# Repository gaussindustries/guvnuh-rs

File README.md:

# Guv'nuh — Micro-Grid Governor Control Platform

A Rust, bare-metal-to-browser control system for a laboratory micro-grid generator set. A hard-real-time STM32H753 governs the machine; an ESP32 bridges it to a Dioxus server and a desktop operator console. Built as the engineering centerpiece for [Gauss Industries](https://gaussindustri.es).

---

## What it does

Guv'nuh closes the loop on a self-excited induction generator (SEIG) driven by a variable-speed prime mover: it holds speed and frequency against changing electrical load, sheds load safely on fault, and streams a full electrical picture — per-phase voltage and current, real power, power factor, DC-bus state — to an operator in real time.

The architecture follows one principle: **the STM32 runs the machine; everything else observes and commands.** Safety-critical decisions (overspeed, load rejection, over-voltage/current) are computed and acted on locally, on-device, with no dependence on the network being up. The ESP32 relays; the server stores; the terminal analyzes. Comms can drop without the machine ever losing control.

---

## System architecture

```
  ┌─────────────┐   UART/COBS    ┌──────────┐    TCP/COBS    ┌──────────────┐   HTTP    ┌───────────────┐
  │  STM32H753  │◄──────────────►│  ESP32   │◄──────────────►│ Dioxus Server│◄─────────►│ Desktop Term. │
  │  (RTIC 2)   │  telemetry ▲   │ (Embassy)│  telemetry ▲   │   + SurrealDB│           │  (Dioxus)     │
  │  the machine│  commands  ▼   │  bridge  │  commands  ▼   │   store/API  │           │  operator UI  │
  └─────────────┘                └──────────┘                └──────────────┘           └───────────────┘
        │
        ├─ dual ADS131M04 (3-phase V/I + DC bus) — coherent sampling
        ├─ TIM1 PWM → prime-mover drive
        ├─ TIM2 QEI → speed encoder
        └─ ordered load bank (2-step resistive, series-ground)
```

**One wire format, end to end.** Every hop serializes the same `shared` crate types with `postcard` + COBS framing — no translation layers, no schema drift between tiers (the whole set rebuilds together when the wire types change).

---

## The STM32H753 firmware — the real-time core

Written against **RTIC 2**, priority-scheduled so the machine stays in tolerance regardless of what else is happening:

| Priority | Task | Rate | Job |
|---|---|---|---|
| 3 | ADC DRDY ISR | ~4 kSPS | Read both ADCs coherently, accumulate sum-of-squares |
| 3 | UART4 RX ISR | event | Drain FIFO, COBS-decode commands into a queue |
| 2 | Safety supervisor | 500 Hz | Overspeed trip + fast electrical protection + load-rejection detection |
| 1 | Control loop | 100 Hz | Governing, full ADC finalize, telemetry assembly |

**Three-phase electrical measurement.** Two ADS131M04 24-bit delta-sigma ADCs share one SPI bus with tied SYNC lines, so all eight channels sample the *same instant* — essential for real-power math (V×I per phase must be coherent). The STM32 computes only the control-critical scalars locally (RMS V/I, real power, PF, frequency, DC bus); harmonics and deep analysis are left to the terminal. Sample rate is a single tunable constant, sized against measured worst-case execution time.

**Load rejection — the fast local path.** A sudden real-power drop means the generator has been unloaded and will overspeed (the defining hazard for a turbine prime mover). The 500 Hz supervisor watches total real power and reacts in-loop — shedding load and faulting — with no network round-trip. This is why the electrical measurements live on the STM32 and not just in telemetry.

**Ordered load bank.** A two-step resistive bank whose second stage draws its ground return *through* the first, so the switching order is a hard electrical constraint. The firmware models this as a state machine that makes an invalid state unrepresentable: it refuses to engage step 2 without step 1, sheds gracefully (2 then 1) under normal operation, and sheds immediately (open 1, dropping both) on E-stop or fault.

---

## The ESP32 bridge

An **Embassy** async firmware that does one job well: shuttle framed bytes between the STM32's UART and a TCP socket to the server, intercepting the link-layer handshake locally so a reboot on either side re-syncs without disturbing the machine. Deliberately dumb — it holds no control logic, matching the "STM32 runs the machine" principle.

---

## Server & operator console

**Dioxus fullstack server** (axum + SurrealDB): ingests telemetry over TCP, stores trials, and exposes a hardware-control API. Telemetry x-axes are derived from a **server-side frame index**, not the device clock — eliminating boot-offset artifacts by construction.

**Desktop operator terminal** (Dioxus): live governing controls (manual / open-loop / closed-loop / scripted profiles), real-time charts (RPM, three-phase voltage and current on shared axes, power and phase-alignment error), a load-bank panel that mirrors the firmware's ordered state machine in the UI, and a trials browser that replays any recorded run with every electrical channel toggleable.

**Scripted profiles** let an operator define an RPM trajectory with load steps scheduled at specific breakpoints — "at t=5s apply half load, at t=10s go full, at t=15s shed" — executed on-device with the ordered switching still enforced.

---

## Tech stack

- **Firmware:** Rust, `no_std`, RTIC 2 (STM32H753), Embassy (ESP32)
- **Wire format:** `postcard` + COBS over UART and TCP; shared type crate
- **Server:** Rust, Dioxus fullstack, axum, SurrealDB (raw HTTP transport)
- **Terminal:** Rust, Dioxus desktop
- **Sensing:** dual TI ADS131M04, external 8.192 MHz coherent clock
- **Networking:** WireGuard-gated admin plane, nginx reverse proxy

---

## Status

Operational: full command + telemetry pipeline live across all four tiers; load bank commanding end-to-end with ordered-switching and E-stop shedding verified in hardware; governing loop running closed on the bench. Three-phase ADC front-end is wired into the firmware (flag-gated) and pending analog front-end bring-up.

**Roadmap:** phase-lock to a grid reference (the alignment view is built and waiting), EtherCAT fieldbus, a SIL-2 certification path, and a micro steam turbine prime mover.

---

## License

© Gauss Industries. All rights reserved.

*Integrity · Innovation · Invention*

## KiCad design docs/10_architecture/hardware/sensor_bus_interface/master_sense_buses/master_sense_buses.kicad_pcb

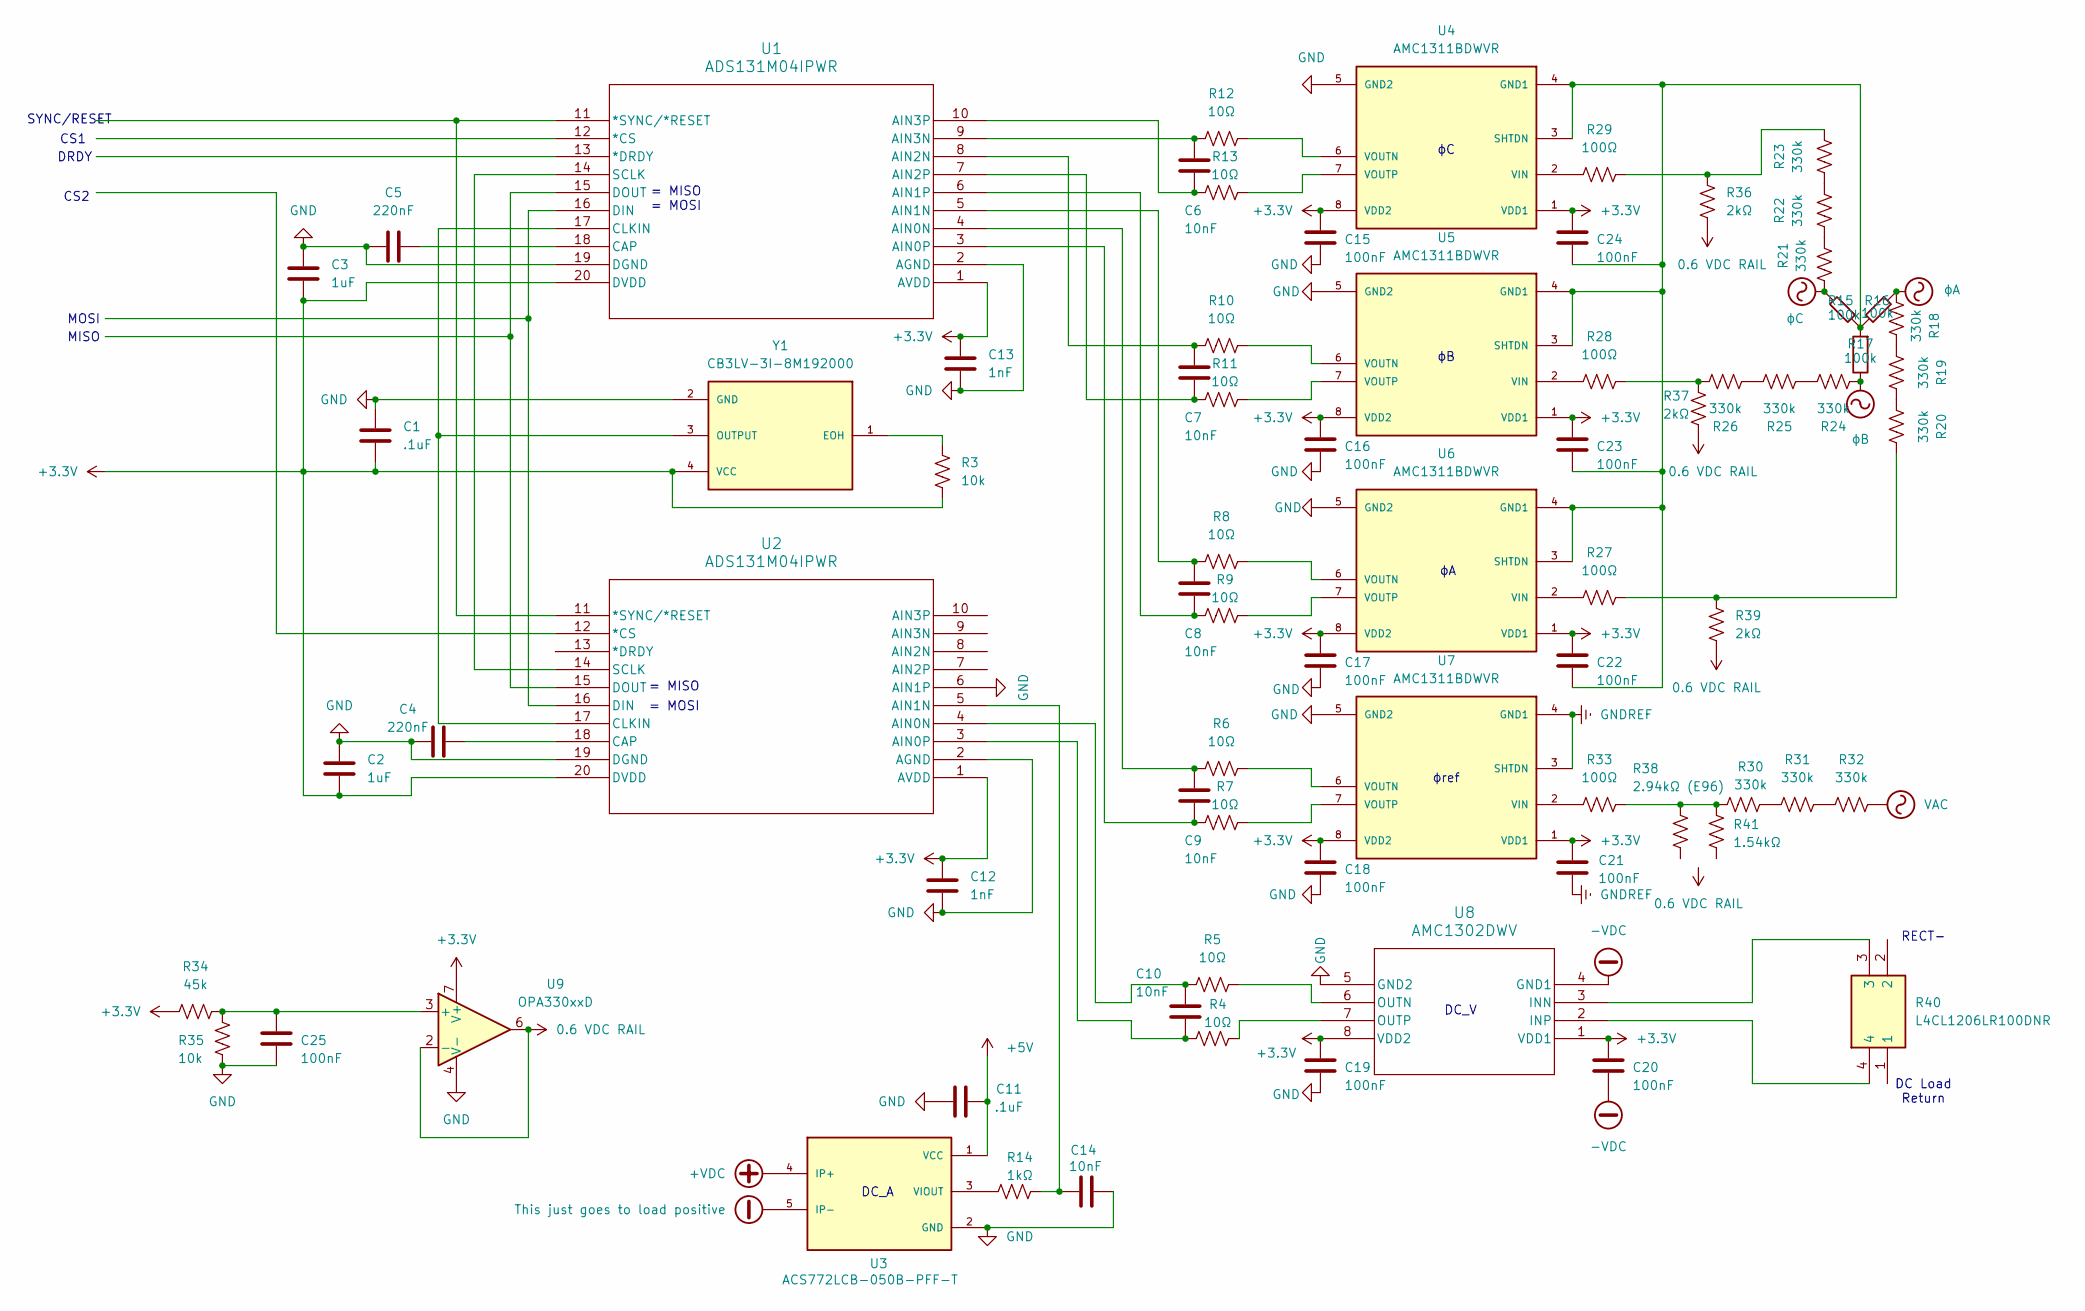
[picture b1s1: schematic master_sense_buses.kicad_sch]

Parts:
C1, C11: .1uF; C_0201_0603Metric
C2, C3: 1uF; C_0201_0603Metric
C4, C5: 220nF; C_0201_0603Metric
C6, C7, C8, C9, C10, C14: 10nF; C_0603_1608Metric
C12, C13: 1nF; C_0201_0603Metric
C15, C16, C17, C18, C19, C20, C21, C22, C23, C24, C25: 100nF; C_0201_0603Metric
R3: 10k; R_0603_1608Metric
R4, R5, R6, R7, R8, R9, R10, R11, R12, R13: 10Ω; R_0603_1608Metric
R14: 1kΩ; R_0603_1608Metric
R15, R16, R17: 100k; R_Axial_DIN0414_L11.9mm_D4.5mm_P15.24mm_Horizontal
R18, R19, R20, R21, R22, R23, R24, R25, R26, R30, R31, R32: 330k; R_1206_3216Metric
R27, R28, R29, R33: 100Ω; R_0805_2012Metric
R34: 45k; R_0603_1608Metric
R35: 10k; R_0201_0603Metric
R36, R37, R39: 2kΩ; R_1206_3216Metric
R38: 2.94kΩ (E96); R_1206_3216Metric
R40: L4CL1206LR100DNR; Mouser Part Number 576-L4CL1206LR100DNR
R41: 1.54kΩ; R_1206_3216Metric
U1, U2: ADS131M04IPWR; PW20_TEX-L
U3: ACS772LCB-050B-PFF-T; XDCR_ACS772LCB-050B-PFF-T; PARTREV 21
U4, U5, U6, U7: AMC1311BDWVR; SOIC127P1150X280-8N; PARTREV A
U8: AMC1302DWV; SOIC8_DMV_TEX-L
U9: OPA330xxD; SOIC-8_3.9x4.9mm_P1.27mm
Y1: CB3LV-3I-8M192000; OSC_CB3LV-3I-8M192000; PARTREV NA

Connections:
0.6 VDC RAIL: R36.2, R37.2, R39.2, U9.2 (-), U9.6
+3.3V: C1.2, C2.2, C3.2, C12.1, C13.1, C15.1, C16.1, C17.1, C18.1, C19.1, C20.1, C21.1, C22.1, C23.1, C24.1, R3.2, R34.2, U1.1 (AVDD), U1.20 (DVDD), U2.1 (AVDD), U2.20 (DVDD), U4.1 (VDD1), U4.8 (VDD2), U5.1 (VDD1), U5.8 (VDD2), U6.1 (VDD1), U6.8 (VDD2), U7.1 (VDD1), U7.8 (VDD2), U8.1 (VDD1), U8.8 (VDD2), U9.7 (V+), Y1.4 (VCC)
+5V: C11.2, U3.1 (VCC)
+VDC: U3.4 (IP+)
-VDC: C20.2, U8.4 (GND1)
GND: C1.1, C2.1, C3.1, C4.2, C5.1, C11.1, C12.2, C13.2, C14.2, C15.2, C16.2, C17.2, C18.2, C19.2, C25.2, R35.2, U1.2 (AGND), U1.19 (DGND), U2.2 (AGND), U2.6 (AIN1P), U2.19 (DGND), U3.2 (GND), U4.5 (GND2), U5.5 (GND2), U6.5 (GND2), U7.5 (GND2), U8.5 (GND2), U9.4 (V-), Y1.2 (GND)
GNDREF: C21.2, U7.3 (SHTDN), U7.4 (GND1)
unnamed: R18.1, R19.2
unnamed: R19.1, R20.2
unnamed: R20.1, R27.1, R39.1
unnamed: R21.1, R22.2
unnamed: R22.1, R23.2
unnamed: R23.1, R29.1, R36.1
unnamed: R24.1, R25.2
unnamed: R25.1, R26.2
unnamed: R26.1, R28.1, R37.1
unnamed: R30.1, R31.2
unnamed: R30.2, R33.1, R38.1, R41.1
unnamed: R31.1, R32.2
unnamed: U1.11 (*SYNC/*RESET), U2.11 (*SYNC/*RESET)
unnamed: C9.1, R6.2, U1.4 (AIN0N)
unnamed: C9.2, R7.2, U1.3 (AIN0P)
unnamed: C8.1, R8.2, U1.5 (AIN1N)
unnamed: C8.2, R9.2, U1.6 (AIN1P)
unnamed: C7.1, R10.2, U1.8 (AIN2N)
unnamed: C7.2, R11.2, U1.7 (AIN2P)
unnamed: C6.1, R12.2, U1.9 (AIN3N)
unnamed: C6.2, R13.2, U1.10 (AIN3P)
unnamed: C5.2, U1.18 (CAP)
unnamed: U1.17 (CLKIN), U2.17 (CLKIN), Y1.3 (OUTPUT)
unnamed: U1.16 (DIN), U2.16 (DIN)
unnamed: U1.15 (DOUT), U2.15 (DOUT)
unnamed: U1.14 (SCLK), U2.14 (SCLK)
unnamed: C10.1, R5.2, U2.4 (AIN0N)
unnamed: C10.2, R4.2, U2.3 (AIN0P)
unnamed: C14.1, R14.1, U2.5 (AIN1N)
unnamed: C4.1, U2.18 (CAP)
unnamed: R14.2, U3.3 (VIOUT)
unnamed: C22.2, C23.2, C24.2, R15.1, R16.2, R17.2, U4.3 (SHTDN), U4.4 (GND1), U5.3 (SHTDN), U5.4 (GND1), U6.3 (SHTDN), U6.4 (GND1)
unnamed: R29.2, U4.2 (VIN)
unnamed: R12.1, U4.6 (VOUTN)
unnamed: R13.1, U4.7 (VOUTP)
unnamed: R28.2, U5.2 (VIN)
unnamed: R10.1, U5.6 (VOUTN)
unnamed: R11.1, U5.7 (VOUTP)
unnamed: R27.2, U6.2 (VIN)
unnamed: R8.1, U6.6 (VOUTN)
unnamed: R9.1, U6.7 (VOUTP)
unnamed: R33.2, U7.2 (VIN)
unnamed: R6.1, U7.6 (VOUTN)
unnamed: R7.1, U7.7 (VOUTP)
unnamed: R40.3, U8.3 (INN)
unnamed: R40.4, U8.2 (INP)
unnamed: R5.1, U8.6 (OUTN)
unnamed: R4.1, U8.7 (OUTP)
unnamed: C25.1, R34.1, R35.1, U9.3 (+)
unnamed: R3.1, Y1.1 (EOH)
This just goes to load positive: U3.5 (IP-)
VAC: R32.1; also elsewhere on the board
ϕA: R16.1, R18.2
ϕB: R17.1, R24.2
ϕC: R15.2, R21.2

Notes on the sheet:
DC_A
DC Load Return
= MISO
= MOSI
RECT-
MOSI
DC_V
DRDY
CS2
ϕref
MISO
CS1
SYNC/RESET

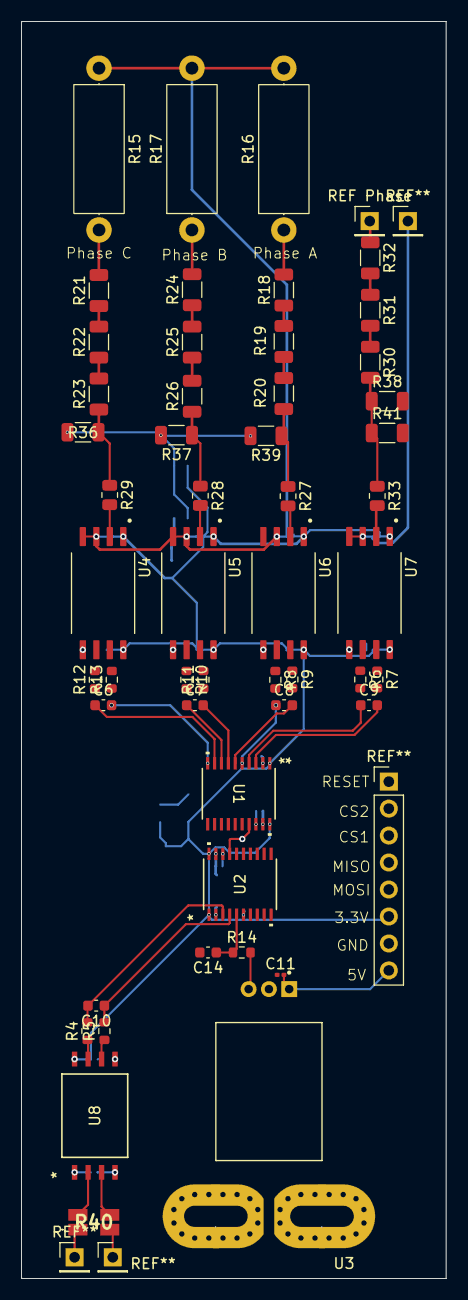
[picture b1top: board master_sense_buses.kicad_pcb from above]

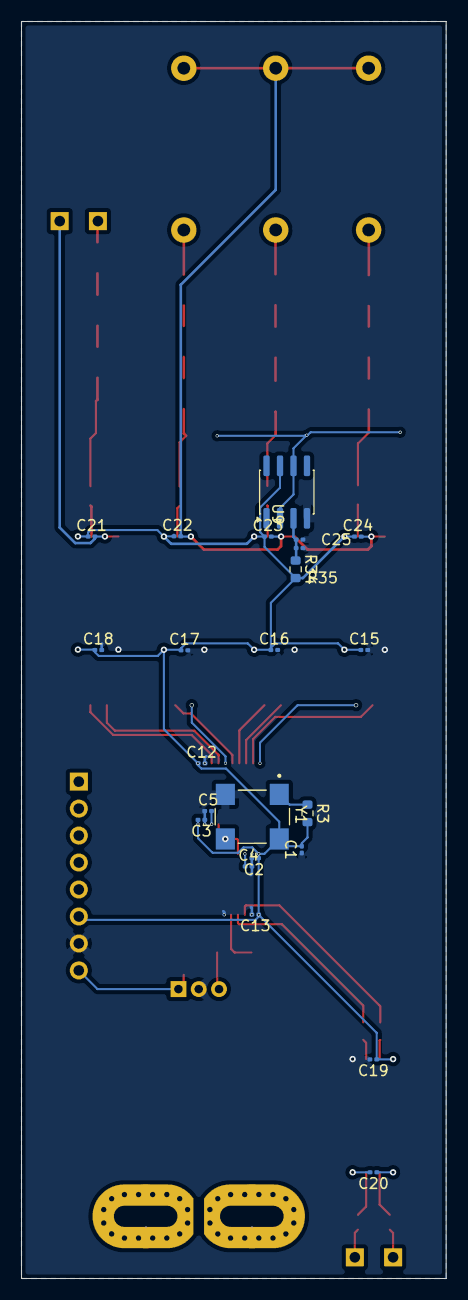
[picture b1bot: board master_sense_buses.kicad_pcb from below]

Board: 2 copper layers, 40.0 x 118.4 mm, 75 parts (23 on the bottom side), 60 nets.

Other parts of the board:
REF Phase: PinHeader_1x01_P2.54mm_Vertical

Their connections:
VAC: REF Phase.1; also elsewhere on the board

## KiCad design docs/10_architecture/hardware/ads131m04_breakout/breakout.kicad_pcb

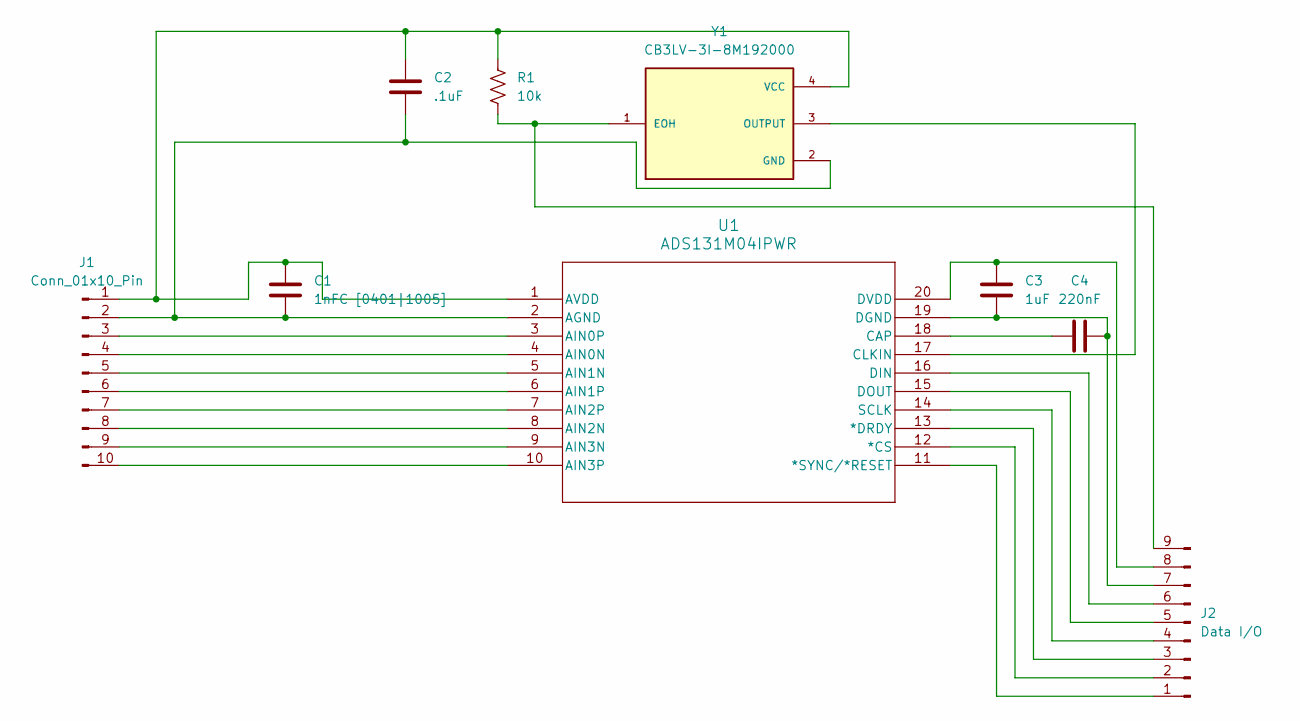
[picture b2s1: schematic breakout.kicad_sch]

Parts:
C1: 1nFC [0401|1005]; C_0402_1005Metric
C2: .1uF; C_0201_0603Metric
C3: 1uF; C_0201_0603Metric
C4: 220nF; C_0402_1005Metric
J1: Conn_01x10_Pin; PinHeader_1x10_P2.54mm_Vertical
J2: Data I/O; PinHeader_1x09_P2.54mm_Vertical
R1: 10k; R_0201_0603Metric
U1: ADS131M04IPWR; PW20_TEX-L
Y1: CB3LV-3I-8M192000; OSC_CB3LV-3I-8M192000; PARTREV NA

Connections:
unnamed: C1.1, C2.1, J1.1, R1.1, U1.1 (AVDD), Y1.4 (VCC)
unnamed: C1.2, C2.2, J1.2, U1.2 (AGND), Y1.2 (GND)
unnamed: J1.3, U1.3 (AIN0P)
unnamed: J1.4, U1.4 (AIN0N)
unnamed: J1.5, U1.5 (AIN1N)
unnamed: J1.6, U1.6 (AIN1P)
unnamed: J1.7, U1.7 (AIN2P)
unnamed: J1.8, U1.8 (AIN2N)
unnamed: J1.9, U1.9 (AIN3N)
unnamed: J1.10, U1.10 (AIN3P)
unnamed: J2.1, U1.11 (*SYNC/*RESET)
unnamed: J2.2, U1.12 (*CS)
unnamed: J2.3, U1.13 (*DRDY)
unnamed: J2.4, U1.14 (SCLK)
unnamed: J2.5, U1.15 (DOUT)
unnamed: J2.6, U1.16 (DIN)
unnamed: C3.2, C4.2, J2.7, U1.19 (DGND)
unnamed: C3.1, J2.8, U1.20 (DVDD)
unnamed: J2.9, R1.2, Y1.1 (EOH)
unnamed: C4.1, U1.18 (CAP)
unnamed: U1.17 (CLKIN), Y1.3 (OUTPUT)

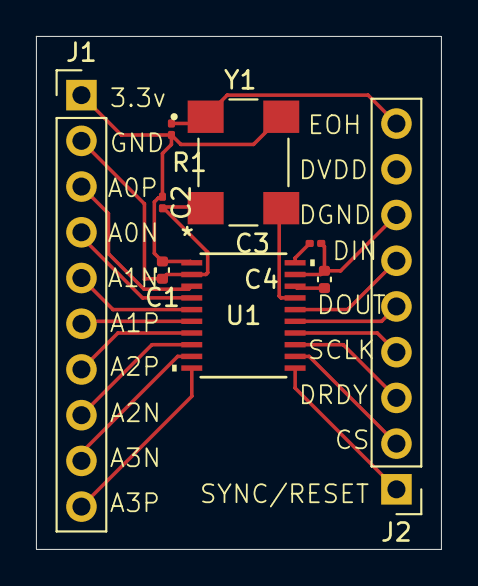
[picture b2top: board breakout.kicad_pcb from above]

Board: 2 copper layers, 22.5 x 28.5 mm, 9 parts (0 on the bottom side), 21 nets.

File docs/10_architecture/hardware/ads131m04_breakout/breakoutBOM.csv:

Reference,Qty,Value,DNP,Exclude from BOM,Exclude from Board,Exclude from Simulation,Exclude from Position Files,Footprint,Datasheet
C1,1,1nFC [0401|1005],0.01294,,,,${EXCLUDE_FROM_POS_FILES},Capacitor_SMD:C_0402_1005Metric,
C2,1,.1uF,0.00622,,,,${EXCLUDE_FROM_POS_FILES},Capacitor_SMD:C_0201_0603Metric,
C3,1,1uF,0.11860,,,,${EXCLUDE_FROM_POS_FILES},Capacitor_SMD:C_0201_0603Metric,
C4,1,220nF,0.00874,,,,${EXCLUDE_FROM_POS_FILES},Capacitor_SMD:C_0402_1005Metric,
J1,1,Conn_01x19_Pin,11.4,,,,${EXCLUDE_FROM_POS_FILES},Connector_PinHeader_2.54mm:PinHeader_1x10_P2.54mm_Vertical,
R1,1,10k,0.01305,,,,${EXCLUDE_FROM_POS_FILES},Resistor_SMD:R_0201_0603Metric,https://www.vishay.com/docs/20035/dcrcwe3.pdf
U1,1,ADS131M04IPWR,5.29,,,,${EXCLUDE_FROM_POS_FILES},Analog_DAC:PW20_TEX-L,https://www.ti.com/lit/gpn/ads131m04
Y1,1,CB3LV-3I-8M192000,1.38,,9.292 each board,,${EXCLUDE_FROM_POS_FILES},Oscillator:OSC_CB3LV-3I-8M192000,
,,,6.82081,with pins = 18.22081,w board wo pins = 16.11281,board w pins = 27.51281,,,

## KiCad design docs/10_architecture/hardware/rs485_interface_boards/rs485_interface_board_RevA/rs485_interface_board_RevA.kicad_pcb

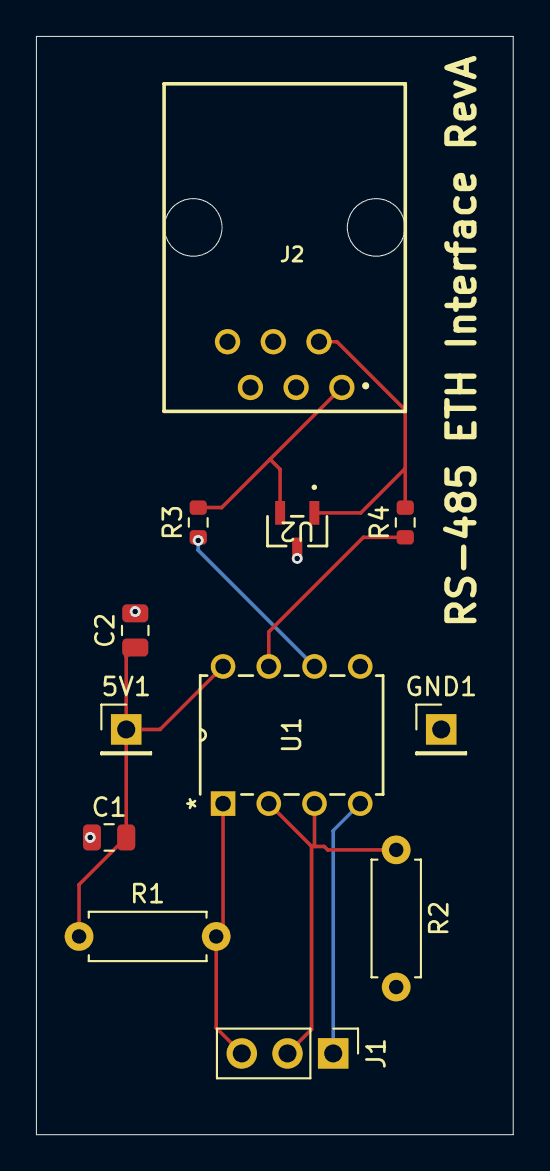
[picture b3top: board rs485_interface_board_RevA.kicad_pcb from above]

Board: 2 copper layers, 26.5 x 61.0 mm, 12 parts (0 on the bottom side), 9 nets.

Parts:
5V1: Conn_01x01; PinHeader_1x01_P2.54mm_Vertical
C1, C2: 100 nf; C_0805_2012Metric
GND1: Conn_01x01; PinHeader_1x01_P2.54mm_Vertical
J1: Conn_01x03; PinHeader_1x03_P2.54mm_Vertical
J2: 615006141121
R1, R2: 10k; R_Axial_DIN0207_L6.3mm_D2.5mm_P7.62mm_Horizontal
R3, R4: 10 Ohm; R_0603_1608Metric
U1: SN65HVD3082EP; sn65hvd3082
U2: SM712.TCT; SOT23_SEM

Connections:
+5V: 5V1.1, C1.2, C2.1, R1.1, U1.8 (VCC)
GND: C1.1, C2.2, GND1.1, J2.3, R2.2, U1.5 (GND), U2.3
unnamed: J1.1, U1.4 (D)
unnamed: J1.2, R2.1, U1.2 (*RE), U1.3 (DE)
unnamed: J1.3, R1.2, U1.1 (R)
unnamed: J2.1, R3.2, U2.2
unnamed: J2.2, R4.2, U2.1
unnamed: R3.1, U1.6 (A)
unnamed: R4.1, U1.7 (B)

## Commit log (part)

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2025-07-07 Init commit – charter, diagrams, CI, docs
2025-07-09 updated master sketch, organized, min vibration
2025-07-09 Added ESP32 Reference Material
2025-07-09 Paved roads to success
2025-10-26 configured linker scripts, simple led blink test
2025-10-26 updated build, prog, & debug commands
2025-10-26 fixed ld2 not blinking
2025-12-11 updated from c/cpp branch
2026-01-15 updated state mod.rs, embedded boot sequence in it's respective file, refined main.rs
2026-01-20 implemented basic logic for pwm for motor spin
2026-02-24 added relay pin & basic safety functionality
2026-03-03 implemented RPM monitor & amt102-v inputs via QEI
2026-03-11 switched to probe-rs for flash/defmt, fixed u64 mismatch in mono timing, fixed negative rpm
2026-03-11 improved rpm calculation
2026-03-11 initialized esp32 logic & build, cleaned config for stm32
2026-03-12 added LED indication for rx (esp32)
2026-03-12 implemented basic UART handshake to ensure stm32 will wait for esp32, or vise versa
2026-03-12 implemented STM32 → UART → ESP32 → WiFi → TCP datapipline
2026-03-17 updated to use data pipeline: STM32 → UART → ESP32 → TCP → Server → SurrealDB
2026-03-21 refined logic to recieve Start command via desktop terminal
2026-03-22 updated readme to reflect current system
2026-05-28 added motor generics, prelude for granular control of trials/running state, live control, updated models to reflect changes
